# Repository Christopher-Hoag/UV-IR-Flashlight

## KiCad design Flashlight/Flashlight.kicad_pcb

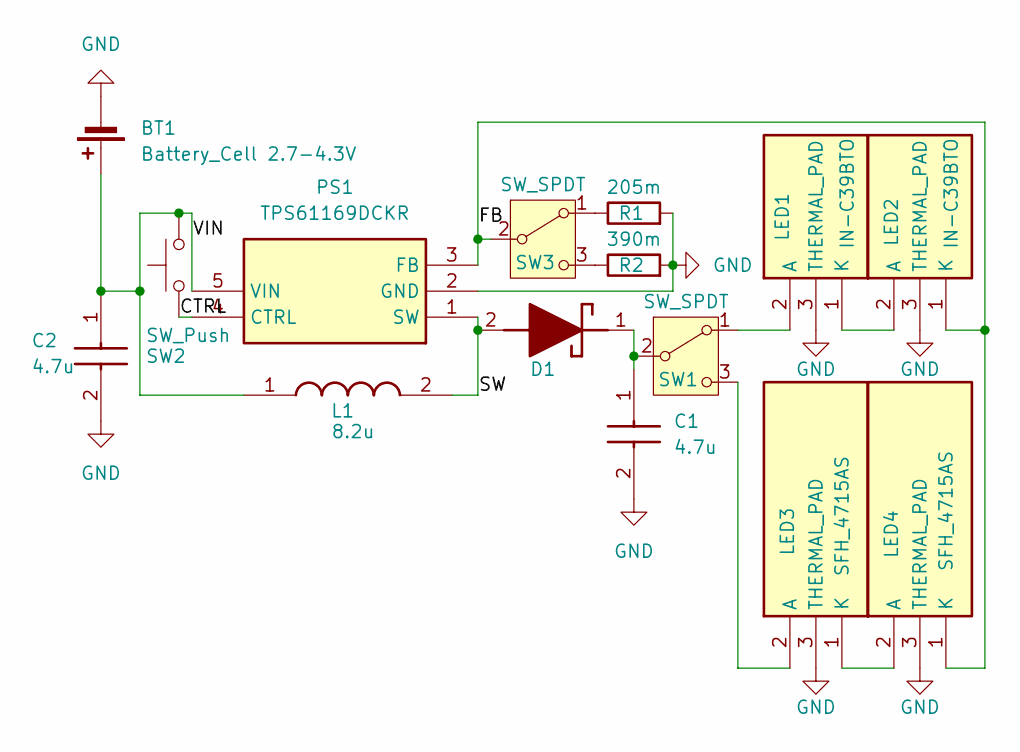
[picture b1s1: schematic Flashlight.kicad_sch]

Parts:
BT1: Battery_Cell 2.7-4.3V; SolderWire-0.5sqmm_1x02_P4.6mm_D0.9mm_OD2.1mm
C1, C2: 4.7u; CAPC2012X140N; Mouser Part Number 187-CL21A475KAQNNNE
D1: CUHS20S30,H3F; CUHS20S40H3F; Mouser Part Number 757-CUHS20S30H3F
L1: 8.2u; 74438357082; Mouser Part Number 710-74438357082
LED1, LED2: IN-C39BTO; IN-C39BTOU2_Landing_Pad; Mouser Part Number 743-IN-C39BTOU2
LED3, LED4: SFH_4715AS; SFH 4715AS; Mouser Part Number 720-SFH4715AS
PS1: TPS61169DCKR; SOT65P210X110-5N; Mouser Part Number 595-TPS61169DCKR
R1: 205m; R_1210_3225Metric_Pad1.30x2.65mm_HandSolder
R2: 390m; R_1210_3225Metric_Pad1.30x2.65mm_HandSolder
SW1: SW_SPDT; SolderWire-0.5sqmm_1x03_P4.6mm_D0.9mm_OD2.1mm
SW2: SW_Push; SolderWire-0.5sqmm_1x02_P4.6mm_D0.9mm_OD2.1mm
SW3: SW_SPDT; DPDT Switch

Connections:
/CTRL: PS1.4 (CTRL), SW2.1
/FB: LED2.1 (K), LED4.1 (K), PS1.3 (FB), SW3.2 (B)
/SW: D1.2 (A), L1.2, PS1.1 (SW)
/VIN: BT1.1 (+), C2.1, L1.1, PS1.5 (VIN), SW2.2
GND: BT1.2 (-), C1.2, C2.2, LED1.3 (THERMAL_PAD), LED2.3 (THERMAL_PAD), LED3.3 (THERMAL_PAD), LED4.3 (THERMAL_PAD), PS1.2 (GND), R1.2, R2.2
unnamed: C1.1, D1.1 (K), SW1.2 (B)
unnamed: LED1.2 (A), SW1.1 (A)
unnamed: LED1.1 (K), LED2.2 (A)
unnamed: LED3.2 (A), SW1.3 (C)
unnamed: LED3.1 (K), LED4.2 (A)
unnamed: R1.1, SW3.1 (A)
unnamed: R2.1, SW3.3 (C)

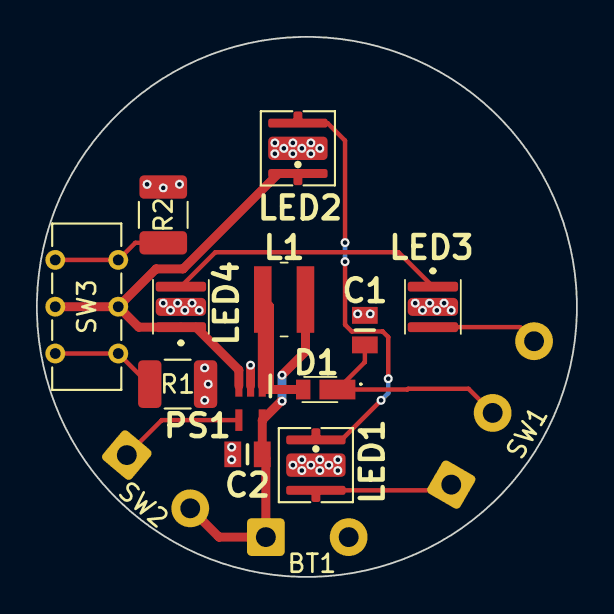
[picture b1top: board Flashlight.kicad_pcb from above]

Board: 2 copper layers, 30.0 x 30.0 mm, 15 parts (0 on the bottom side), 12 nets.

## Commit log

2024-04-22 KiCAD files
2024-04-22 Fusion 360 Design
